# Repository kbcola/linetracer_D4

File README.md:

# linetracer_D4_8
KCCT-D4 ライントレーサー実験 8班

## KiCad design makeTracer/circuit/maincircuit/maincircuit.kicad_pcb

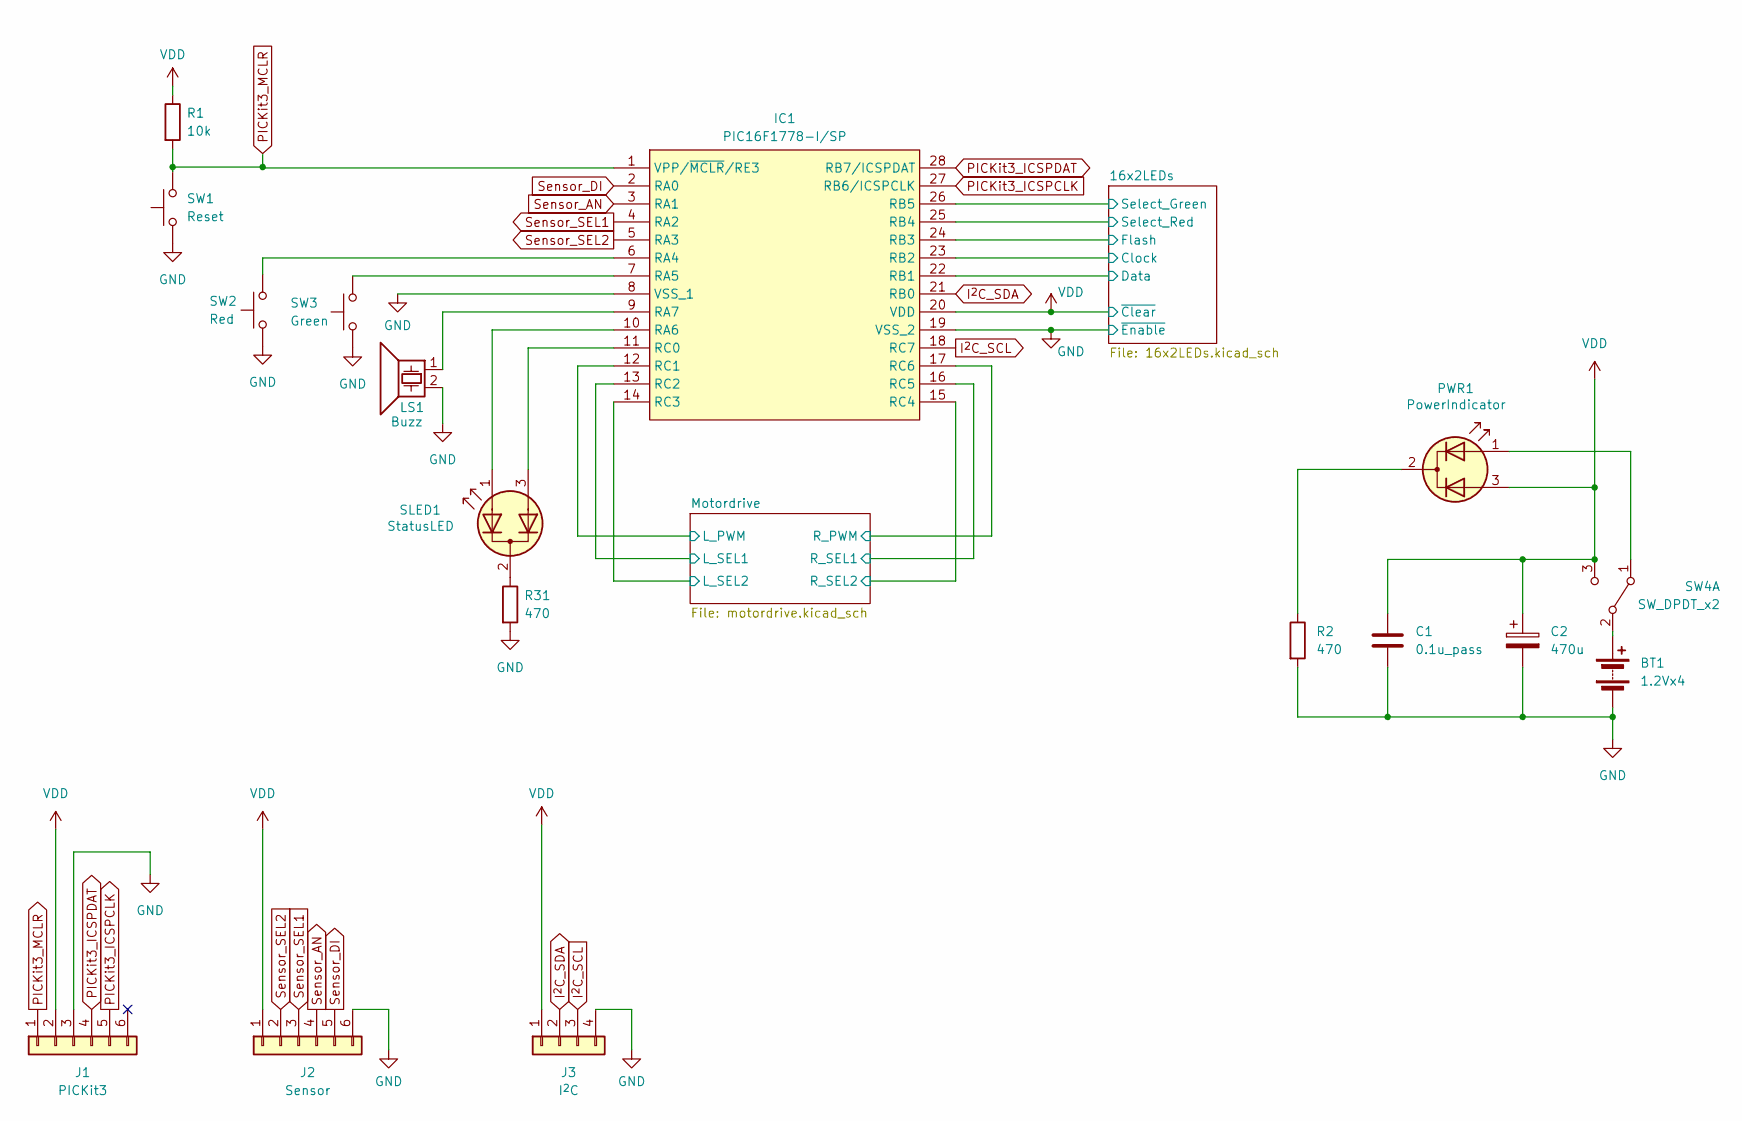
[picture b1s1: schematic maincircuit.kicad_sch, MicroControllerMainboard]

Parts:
BT1: 1.2Vx4; PinHeader_1x02_P2.54mm_Vertical
C1: 0.1u_pass; C_Disc_D5.0mm_W2.5mm_P2.50mm
C2: 470u; CP_Radial_D8.0mm_P3.50mm
IC1: PIC16F1778-I/SP; DIP-28_W7.62mm_Socket_LongPads
J1: PICKit3; PinHeader_1x06_P2.54mm_Vertical
J2: Sensor; SHDR6W69P0X250_1X6_1500X490X1040P
J3: I^{2}C; HDRV4W69P0X250_1X4_1000X500X1040P
LS1: Buzz; Buzzer_TDK_PS1240P02BT_D12.2mm_H6.5mm
PWR1: PowerIndicator; LED_D3.0mm-3
R1: 10k; R_Axial_DIN0207_L6.3mm_D2.5mm_P2.54mm_Vertical
R2: 470; R_Axial_DIN0207_L6.3mm_D2.5mm_P5.08mm_Vertical
R31: 470; R_Axial_DIN0207_L6.3mm_D2.5mm_P7.62mm_Horizontal
SLED1: StatusLED; LED_D3.0mm-3
SW1: Reset; SW_PUSH_6mm_H5mm
SW2: Red; SW_PUSH_6mm_H5mm
SW3: Green; SW_PUSH_6mm_H5mm
SW4: SW_DPDT_x2; ToggleSW_3pin

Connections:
/16x2LEDs/Clock: IC1.23 (RB2); also elsewhere on the board
/16x2LEDs/Data: IC1.22 (RB1); also elsewhere on the board
/16x2LEDs/Flash: IC1.24 (RB3); also elsewhere on the board
/16x2LEDs/Select_Green: IC1.26 (RB5); also elsewhere on the board
/16x2LEDs/Select_Red: IC1.25 (RB4); also elsewhere on the board
/Motordrive/L_PWM: IC1.12 (RC1); also elsewhere on the board
/Motordrive/L_SEL1: IC1.13 (RC2); also elsewhere on the board
/Motordrive/L_SEL2: IC1.14 (RC3); also elsewhere on the board
/Motordrive/R_PWM: IC1.17 (RC6); also elsewhere on the board
/Motordrive/R_SEL1: IC1.16 (RC5); also elsewhere on the board
/Motordrive/R_SEL2: IC1.15 (RC4); also elsewhere on the board
GND: BT1.2 (-), C1.2, C2.2, IC1.8 (VSS_1), IC1.19 (VSS_2), J1.3, J2.6, J3.4, LS1.2, R2.2, R31.2, SW1.1, SW2.1, SW3.1; also elsewhere on the board
I^{2}C_SCL: IC1.18 (RC7), J3.3
I^{2}C_SDA: IC1.21 (RB0), J3.2
unnamed: BT1.1 (+), SW4.2 (B)
unnamed: IC1.6 (RA4), SW2.2
unnamed: IC1.7 (RA5), SW3.2
unnamed: IC1.10 (RA6), SLED1.1 (A1)
unnamed: IC1.9 (RA7), LS1.1
unnamed: IC1.11 (RC0), SLED1.3 (A2)
unnamed: PWR1.1 (A1), SW4.1 (A)
unnamed: PWR1.2 (K), R2.1
unnamed: R31.1, SLED1.2 (K)
PICKit3_ICSPCLK: IC1.27 (RB6/ICSPCLK), J1.5
PICKit3_ICSPDAT: IC1.28 (RB7/ICSPDAT), J1.4
PICKit3_MCLR: IC1.1 (VPP/~MCLR/RE3), J1.1, R1.2, SW1.2
Sensor_AN: IC1.3 (RA1), J2.4
Sensor_DI: IC1.2 (RA0), J2.5
Sensor_SEL1: IC1.4 (RA2), J2.3
Sensor_SEL2: IC1.5 (RA3), J2.2
VDD: C1.1, C2.1, IC1.20 (VDD), J1.2, J2.1, J3.1, PWR1.3 (A2), R1.1, SW4.3 (C); also elsewhere on the board

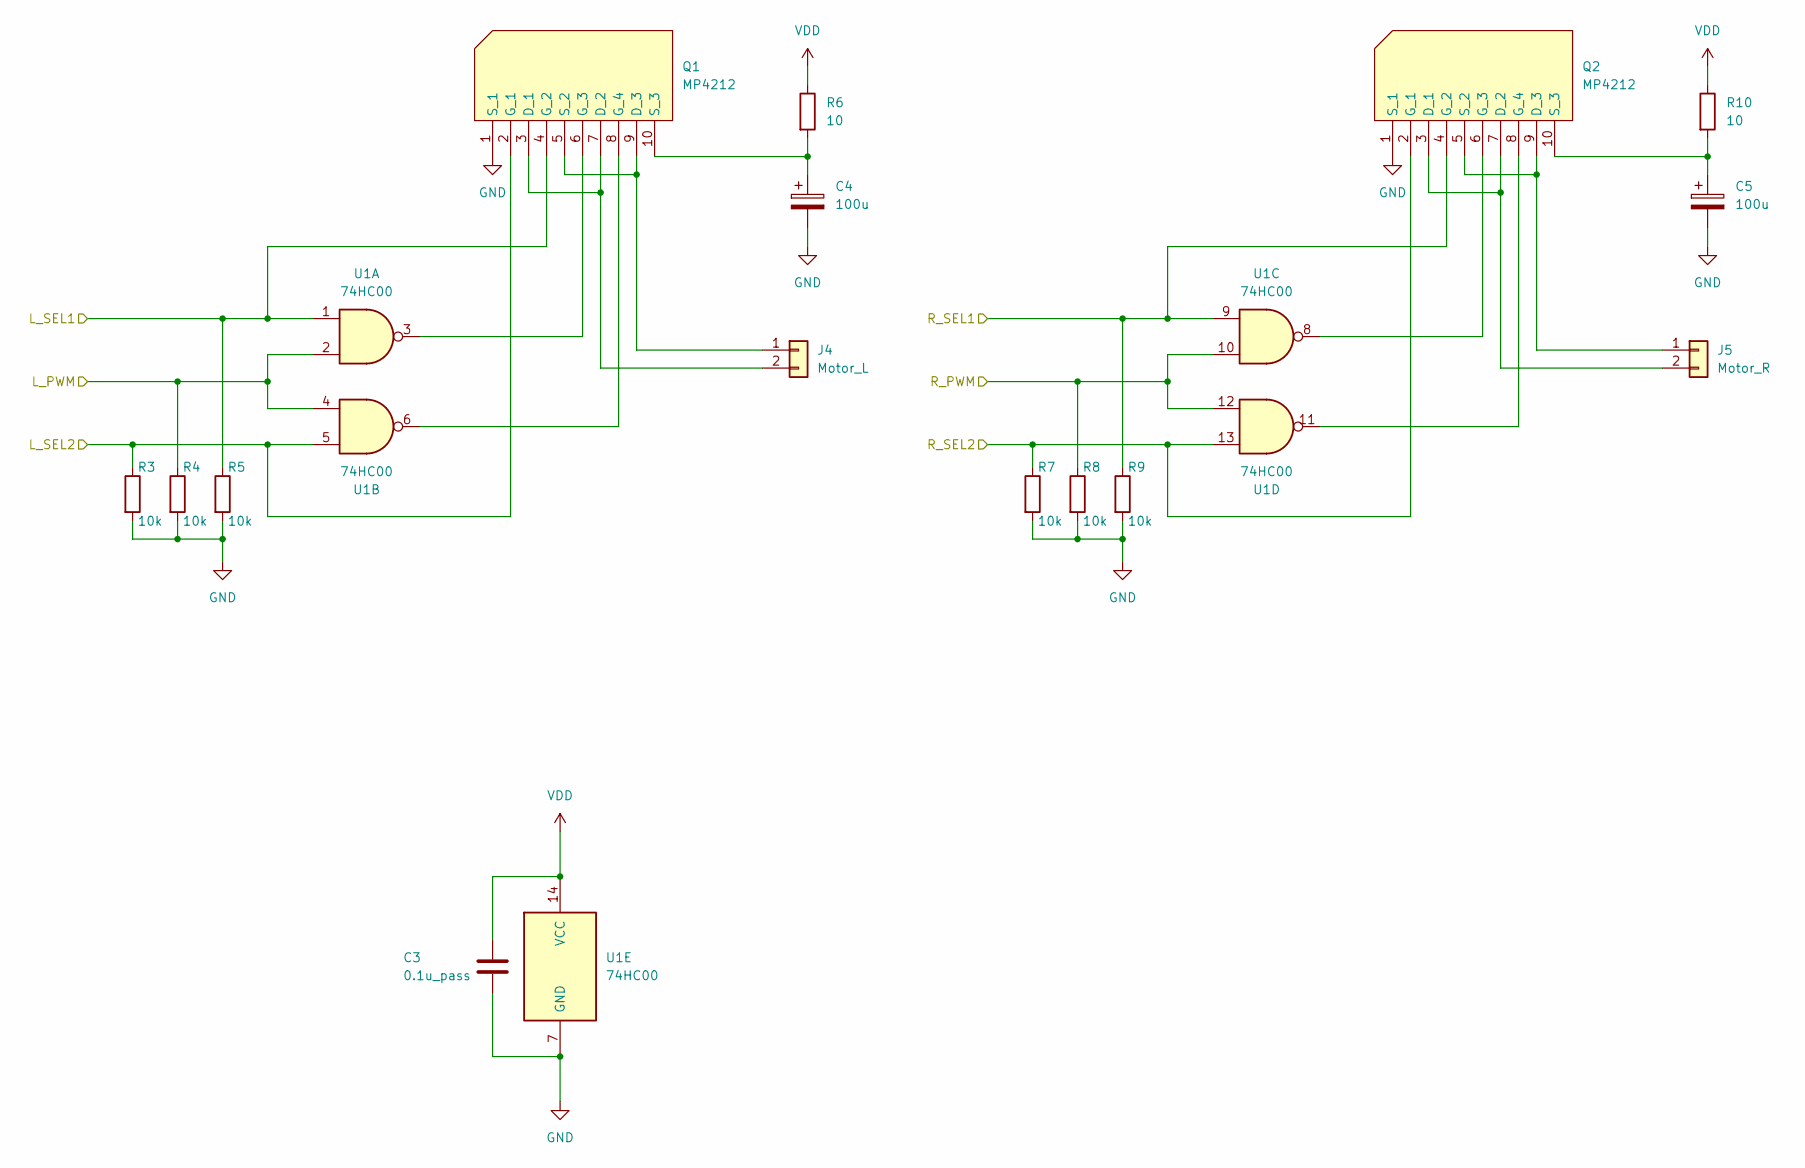
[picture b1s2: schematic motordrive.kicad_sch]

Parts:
C3: 0.1u_pass; C_Disc_D5.0mm_W2.5mm_P2.50mm
C4, C5: 100u; CP_Radial_D5.0mm_P2.00mm
J4: Motor_L; SHDR2W69P0X250_1X2_500X530X1040P
J5: Motor_R; SHDR2W69P0X250_1X2_500X530X1040P
Q1, Q2: MP4212; MP4212_WIDE
R3, R4, R7: 10k; R_Axial_DIN0207_L6.3mm_D2.5mm_P7.62mm_Horizontal
R5: 10k; R_Axial_DIN0207_L6.3mm_D2.5mm_P5.08mm_Vertical
R6: 10; R_Axial_DIN0309_L9.0mm_D3.2mm_P20.32mm_Horizontal
R8, R9: 10k; R_Axial_DIN0207_L6.3mm_D2.5mm_P2.54mm_Vertical
R10: 10; R_Axial_DIN0309_L9.0mm_D3.2mm_P12.70mm_Horizontal
U1: 74HC00; DIP-14_W7.62mm_Socket_LongPads

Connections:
/Motordrive/L_PWM: R4.1, U1.2, U1.4; also elsewhere on the board
/Motordrive/L_SEL1: Q1.4 (G_2), R5.1, U1.1; also elsewhere on the board
/Motordrive/L_SEL2: Q1.2 (G_1), R3.1, U1.5; also elsewhere on the board
/Motordrive/R_PWM: R8.1, U1.10, U1.12; also elsewhere on the board
/Motordrive/R_SEL1: Q2.4 (G_2), R9.1, U1.9; also elsewhere on the board
/Motordrive/R_SEL2: Q2.2 (G_1), R7.1, U1.13; also elsewhere on the board
GND: C3.2, C4.2, C5.2, Q1.1 (S_1), Q2.1 (S_1), R3.2, R4.2, R5.2, R7.2, R8.2, R9.2, U1.7 (GND); also elsewhere on the board
unnamed: J4.1, Q1.5 (S_2), Q1.9 (D_3)
unnamed: J4.2, Q1.3 (D_1), Q1.7 (D_2)
unnamed: J5.1, Q2.5 (S_2), Q2.9 (D_3)
unnamed: J5.2, Q2.3 (D_1), Q2.7 (D_2)
unnamed: Q1.6 (G_3), U1.3
unnamed: Q1.8 (G_4), U1.6
unnamed: C4.1, Q1.10 (S_3), R6.2
unnamed: Q2.6 (G_3), U1.8
unnamed: Q2.8 (G_4), U1.11
unnamed: C5.1, Q2.10 (S_3), R10.2
VDD: C3.1, R6.1, R10.1, U1.14 (VCC); also elsewhere on the board

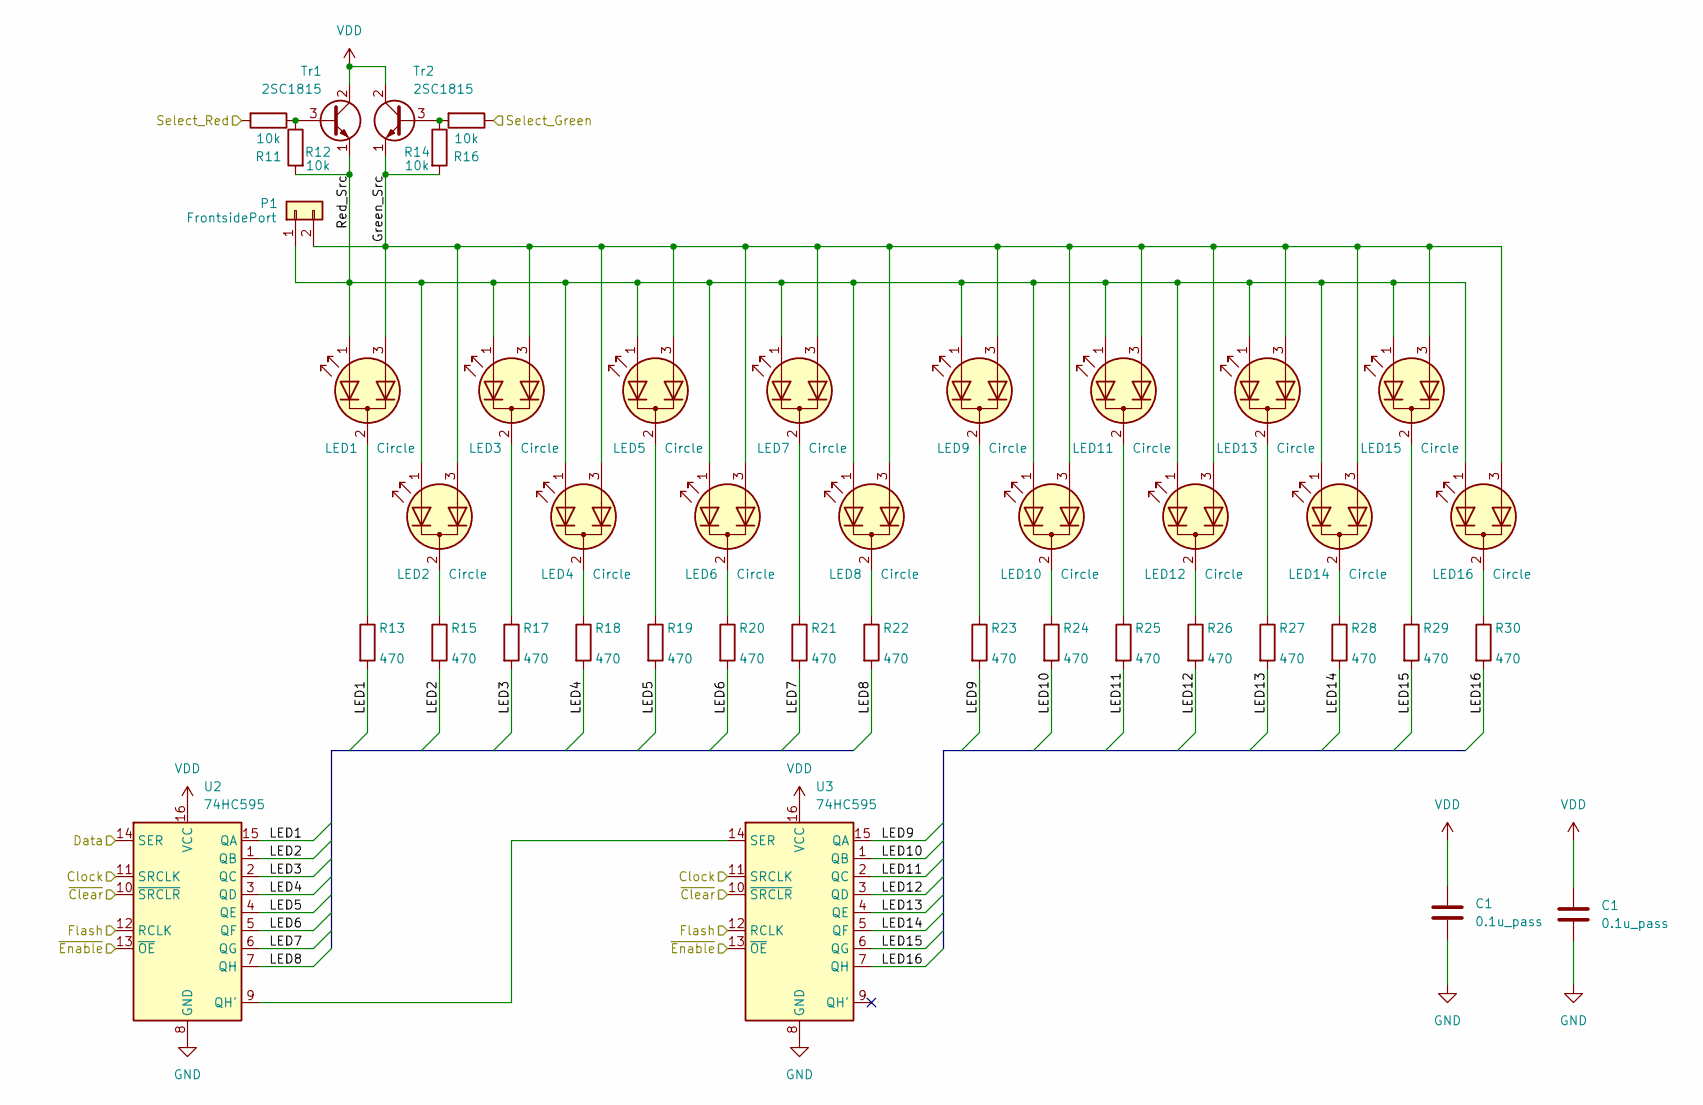
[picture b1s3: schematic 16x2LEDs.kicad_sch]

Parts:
C1: 0.1u_pass; C_Disc_D5.0mm_W2.5mm_P2.50mm
LED1, LED2, LED3, LED4, LED5, LED6, LED7, LED8, LED9, LED10, LED11, LED12, LED13, LED14, LED15, LED16: Circle; LED_D3.0mm-3
P1: FrontsidePort; PinHeader_1x02_P2.54mm_Vertical
R11, R14: 10k; R_Axial_DIN0207_L6.3mm_D2.5mm_P2.54mm_Vertical
R12, R16: 10k; R_Axial_DIN0207_L6.3mm_D2.5mm_P5.08mm_Vertical
R13, R18, R23: 470; R_Axial_DIN0207_L6.3mm_D2.5mm_P10.16mm_Horizontal
R15, R17, R19, R20, R21, R22, R24, R25, R26, R27, R28, R29, R30: 470; R_Axial_DIN0207_L6.3mm_D2.5mm_P7.62mm_Horizontal
Tr1, Tr2: 2SC1815; TO-92_Inline_Wide
U2, U3: 74HC595; DIP-16_W7.62mm_LongPads

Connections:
/16x2LEDs/Clock: U2.11 (SRCLK), U3.11 (SRCLK); also elsewhere on the board
/16x2LEDs/Data: U2.14 (SER); also elsewhere on the board
/16x2LEDs/Flash: U2.12 (RCLK), U3.12 (RCLK); also elsewhere on the board
/16x2LEDs/Green_Src: LED1.3 (A2), LED2.3 (A2), LED3.3 (A2), LED4.3 (A2), LED5.3 (A2), LED6.3 (A2), LED7.3 (A2), LED8.3 (A2), LED9.3 (A2), LED10.3 (A2), LED11.3 (A2), LED12.3 (A2), LED13.3 (A2), LED14.3 (A2), LED15.3 (A2), LED16.3 (A2), P1.2, R14.2, Tr2.1 (E)
/16x2LEDs/LED1: R13.2, U2.15 (QA)
/16x2LEDs/LED2: R15.2, U2.1 (QB)
/16x2LEDs/LED3: R17.2, U2.2 (QC)
/16x2LEDs/LED4: R18.2, U2.3 (QD)
/16x2LEDs/LED5: R19.2, U2.4 (QE)
/16x2LEDs/LED6: R20.2, U2.5 (QF)
/16x2LEDs/LED7: R21.2, U2.6 (QG)
/16x2LEDs/LED8: R22.2, U2.7 (QH)
/16x2LEDs/LED9: R23.2, U3.15 (QA)
/16x2LEDs/LED10: R24.2, U3.1 (QB)
/16x2LEDs/LED11: R25.2, U3.2 (QC)
/16x2LEDs/LED12: R26.2, U3.3 (QD)
/16x2LEDs/LED13: R27.2, U3.4 (QE)
/16x2LEDs/LED14: R28.2, U3.5 (QF)
/16x2LEDs/LED15: R29.2, U3.6 (QG)
/16x2LEDs/LED16: R30.2, U3.7 (QH)
/16x2LEDs/Red_Src: LED1.1 (A1), LED2.1 (A1), LED3.1 (A1), LED4.1 (A1), LED5.1 (A1), LED6.1 (A1), LED7.1 (A1), LED8.1 (A1), LED9.1 (A1), LED10.1 (A1), LED11.1 (A1), LED12.1 (A1), LED13.1 (A1), LED14.1 (A1), LED15.1 (A1), LED16.1 (A1), P1.1, R12.2, Tr1.1 (E)
/16x2LEDs/Select_Green: R16.1; also elsewhere on the board
/16x2LEDs/Select_Red: R11.2; also elsewhere on the board
GND: C1.2, U2.8 (GND), U2.13 (~OE), U3.8 (GND), U3.13 (~OE); also elsewhere on the board
unnamed: LED1.2 (K), R13.1
unnamed: LED2.2 (K), R15.1
unnamed: LED3.2 (K), R17.1
unnamed: LED4.2 (K), R18.1
unnamed: LED5.2 (K), R19.1
unnamed: LED6.2 (K), R20.1
unnamed: LED7.2 (K), R21.1
unnamed: LED8.2 (K), R22.1
unnamed: LED9.2 (K), R23.1
unnamed: LED10.2 (K), R24.1
unnamed: LED11.2 (K), R25.1
unnamed: LED12.2 (K), R26.1
unnamed: LED13.2 (K), R27.1
unnamed: LED14.2 (K), R28.1
unnamed: LED15.2 (K), R29.1
unnamed: LED16.2 (K), R30.1
unnamed: R11.1, R12.1, Tr1.3 (B)
unnamed: R14.1, R16.2, Tr2.3 (B)
unnamed: U2.9 (QH'), U3.14 (SER)
VDD: C1.1, Tr1.2 (C), Tr2.2 (C), U2.10 (~SRCLR), U2.16 (VCC), U3.10 (~SRCLR), U3.16 (VCC); also elsewhere on the board

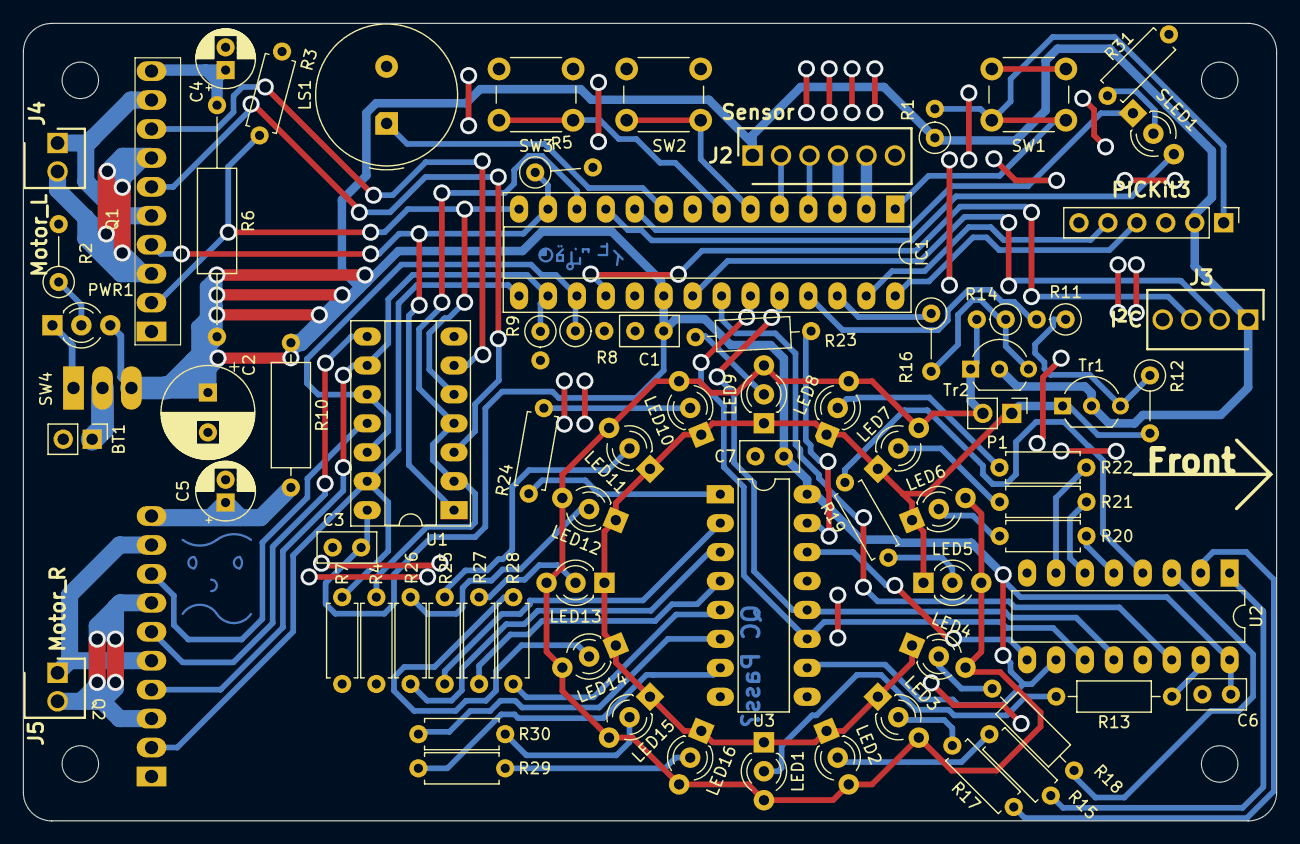
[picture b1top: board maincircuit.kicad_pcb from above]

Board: 2 copper layers, 110.0 x 70.0 mm, 76 parts (1 on the bottom side), 78 nets.

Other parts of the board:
C6, C7: 0.1u_pass; C_Disc_D5.0mm_W2.5mm_P2.50mm

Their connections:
GND: C6.2, C7.2; also elsewhere on the board
VDD: C6.1, C7.1; also elsewhere on the board

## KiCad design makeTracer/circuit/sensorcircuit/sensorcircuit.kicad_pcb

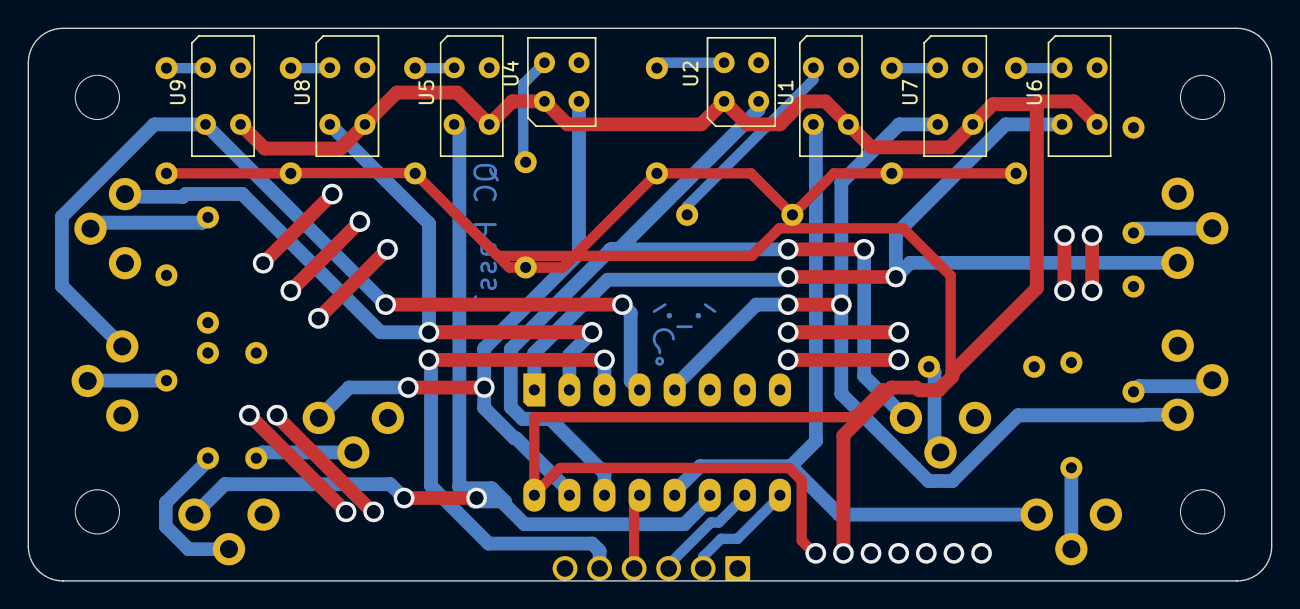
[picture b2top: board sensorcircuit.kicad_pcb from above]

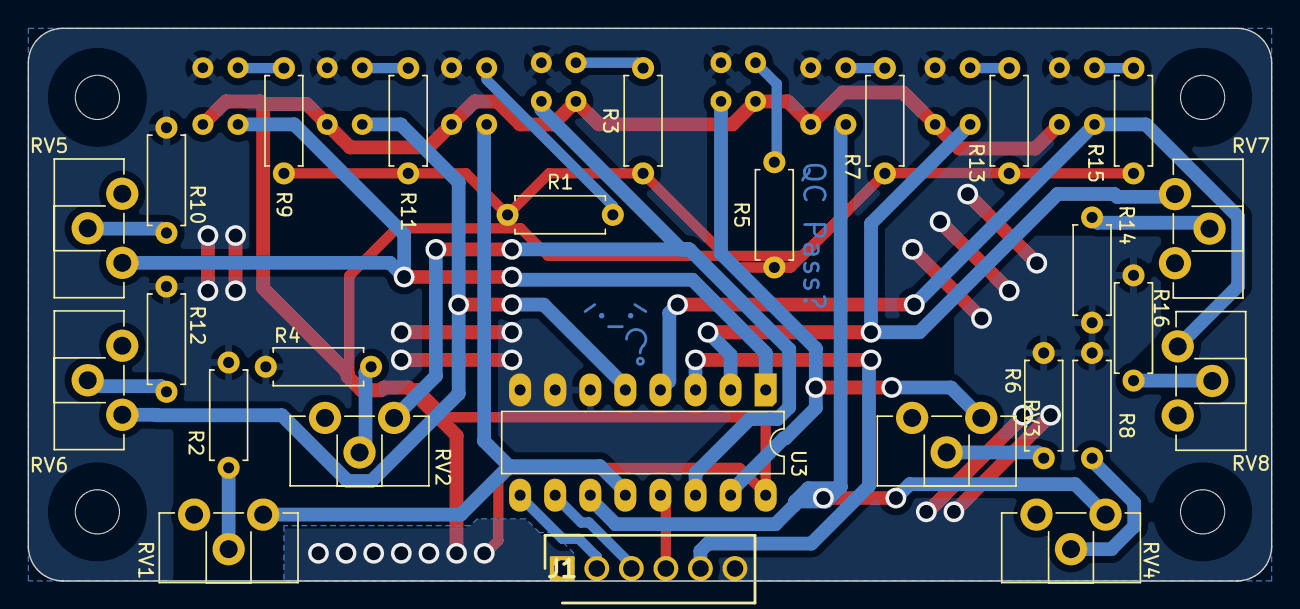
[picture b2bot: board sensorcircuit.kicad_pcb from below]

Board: 2 copper layers, 90.0 x 40.0 mm, 34 parts (26 on the bottom side), 30 nets.

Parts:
J1: Maincircuit; SHDR6W69P0X250_1X6_1500X490X1040P
R1, R3, R5, R7, R9, R11, R13, R15: 220; R_Axial_DIN0207_L6.3mm_D2.5mm_P7.62mm_Horizontal
R2, R4, R6, R8, R10, R12, R14, R16: 100k; R_Axial_DIN0207_L6.3mm_D2.5mm_P7.62mm_Horizontal
RV1, RV2, RV3, RV4, RV5, RV6, RV7, RV8: 50k; Potentiometer_ACP_CA9-H2,5_Horizontal
U1, U5, U6, U7, U8, U9: LBR-127HLD
U2, U4: RPR-220
U3: 4052; DIP-16_W7.62mm_LongPads

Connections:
/Ann_0: RV1.1, U1.3, U3.12 (X0)
/Ann_1: RV2.1, U2.3, U3.14 (X1)
/Ann_2: RV3.1, U3.15 (X2), U4.3
/Ann_3: RV4.1, U3.11 (X3), U5.3
/Dig_0: RV5.1, U3.1 (Y0), U6.3
/Dig_1: RV6.1, U3.5 (Y1), U7.3
/Dig_2: RV7.1, U3.2 (Y2), U8.3
/Dig_3: RV8.1, U3.4 (Y3), U9.3
Analog_Process: J1.4, U3.13 (X)
Digital_Process: J1.5, U3.3 (Y)
GND: J1.6, R2.2, R4.2, R6.2, R8.2, R10.2, R12.2, R14.2, R16.2, U1.2, U2.2, U3.6 (Inh), U3.7 (VEE), U3.8 (VSS), U4.2, U5.2, U6.2, U7.2, U8.2, U9.2
unnamed: R1.2, U1.1
unnamed: R2.1, RV1.2
unnamed: R3.2, U2.1
unnamed: R4.1, RV2.2
unnamed: R5.2, U4.1
unnamed: R6.1, RV3.2
unnamed: R7.2, U5.1
unnamed: R8.1, RV4.2
unnamed: R9.2, U6.1
unnamed: R10.1, RV5.2
unnamed: R11.2, U7.1
unnamed: R12.1, RV6.2
unnamed: R13.2, U8.1
unnamed: R14.1, RV7.2
unnamed: R15.2, U9.1
unnamed: R16.1, RV8.2
Port_SEL1: J1.3, U3.10 (A)
Port_SEL2: J1.2, U3.9 (B)
VDD: J1.1, R1.1, R3.1, R5.1, R7.1, R9.1, R11.1, R13.1, R15.1, U1.4, U2.4, U3.16 (VDD), U4.4, U5.4, U6.4, U7.4, U8.4, U9.4

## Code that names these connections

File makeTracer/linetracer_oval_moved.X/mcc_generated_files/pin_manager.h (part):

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// get/set channel_AN0 aliases
#define channel_AN0_TRIS                 TRISAbits.TRISA0
#define channel_AN0_LAT                  LATAbits.LATA0
#define channel_AN0_PORT                 PORTAbits.RA0
#define channel_AN0_WPU                  WPUAbits.WPUA0
#define channel_AN0_OD                   ODCONAbits.ODA0
#define channel_AN0_ANS                  ANSELAbits.ANSA0
#define channel_AN0_SetHigh()            do { LATAbits.LATA0 = 1; } while(0)
#define channel_AN0_SetLow()             do { LATAbits.LATA0 = 0; } while(0)
#define channel_AN0_Toggle()             do { LATAbits.LATA0 = ~LATAbits.LATA0; } while(0)
#define channel_AN0_GetValue()           PORTAbits.RA0
#define channel_AN0_SetDigitalInput()    do { TRISAbits.TRISA0 = 1; } while(0)
#define channel_AN0_SetDigitalOutput()   do { TRISAbits.TRISA0 = 0; } while(0)
#define channel_AN0_SetPullup()          do { WPUAbits.WPUA0 = 1; } while(0)
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// get/set channel_AN1 aliases
#define channel_AN1_TRIS                 TRISAbits.TRISA1
#define channel_AN1_LAT                  LATAbits.LATA1
#define channel_AN1_PORT                 PORTAbits.RA1
#define channel_AN1_WPU                  WPUAbits.WPUA1
#define channel_AN1_OD                   ODCONAbits.ODA1
#define channel_AN1_ANS                  ANSELAbits.ANSA1
#define channel_AN1_SetHigh()            do { LATAbits.LATA1 = 1; } while(0)
#define channel_AN1_SetLow()             do { LATAbits.LATA1 = 0; } while(0)
#define channel_AN1_Toggle()             do { LATAbits.LATA1 = ~LATAbits.LATA1; } while(0)
#define channel_AN1_GetValue()           PORTAbits.RA1
#define channel_AN1_SetDigitalInput()    do { TRISAbits.TRISA1 = 1; } while(0)
#define channel_AN1_SetDigitalOutput()   do { TRISAbits.TRISA1 = 0; } while(0)
#define channel_AN1_SetPullup()          do { WPUAbits.WPUA1 = 1; } while(0)
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// get/set SENS_SEL1 aliases
#define SENS_SEL1_TRIS                 TRISAbits.TRISA2
#define SENS_SEL1_LAT                  LATAbits.LATA2
#define SENS_SEL1_PORT                 PORTAbits.RA2
#define SENS_SEL1_WPU                  WPUAbits.WPUA2
#define SENS_SEL1_OD                   ODCONAbits.ODA2
#define SENS_SEL1_ANS                  ANSELAbits.ANSA2
#define SENS_SEL1_SetHigh()            do { LATAbits.LATA2 = 1; } while(0)
#define SENS_SEL1_SetLow()             do { LATAbits.LATA2 = 0; } while(0)
#define SENS_SEL1_Toggle()             do { LATAbits.LATA2 = ~LATAbits.LATA2; } while(0)
#define SENS_SEL1_GetValue()           PORTAbits.RA2
#define SENS_SEL1_SetDigitalInput()    do { TRISAbits.TRISA2 = 1; } while(0)
#define SENS_SEL1_SetDigitalOutput()   do { TRISAbits.TRISA2 = 0; } while(0)
#define SENS_SEL1_SetPullup()          do { WPUAbits.WPUA2 = 1; } while(0)
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// get/set SENS_SEL2 aliases
#define SENS_SEL2_TRIS                 TRISAbits.TRISA3
#define SENS_SEL2_LAT                  LATAbits.LATA3
#define SENS_SEL2_PORT                 PORTAbits.RA3
#define SENS_SEL2_WPU                  WPUAbits.WPUA3
#define SENS_SEL2_OD                   ODCONAbits.ODA3
#define SENS_SEL2_ANS                  ANSELAbits.ANSA3
#define SENS_SEL2_SetHigh()            do { LATAbits.LATA3 = 1; } while(0)
#define SENS_SEL2_SetLow()             do { LATAbits.LATA3 = 0; } while(0)
#define SENS_SEL2_Toggle()             do { LATAbits.LATA3 = ~LATAbits.LATA3; } while(0)
#define SENS_SEL2_GetValue()           PORTAbits.RA3
#define SENS_SEL2_SetDigitalInput()    do { TRISAbits.TRISA3 = 1; } while(0)
#define SENS_SEL2_SetDigitalOutput()   do { TRISAbits.TRISA3 = 0; } while(0)
#define SENS_SEL2_SetPullup()          do { WPUAbits.WPUA3 = 1; } while(0)
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// get/set SW1 aliases
#define SW1_TRIS                 TRISAbits.TRISA4
#define SW1_LAT                  LATAbits.LATA4
#define SW1_PORT                 PORTAbits.RA4
#define SW1_WPU                  WPUAbits.WPUA4
#define SW1_OD                   ODCONAbits.ODA4
#define SW1_ANS                  ANSELAbits.ANSA4
#define SW1_SetHigh()            do { LATAbits.LATA4 = 1; } while(0)
#define SW1_SetLow()             do { LATAbits.LATA4 = 0; } while(0)
#define SW1_Toggle()             do { LATAbits.LATA4 = ~LATAbits.LATA4; } while(0)
#define SW1_GetValue()           PORTAbits.RA4
#define SW1_SetDigitalInput()    do { TRISAbits.TRISA4 = 1; } while(0)
#define SW1_SetDigitalOutput()   do { TRISAbits.TRISA4 = 0; } while(0)
#define SW1_SetPullup()          do { WPUAbits.WPUA4 = 1; } while(0)
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// get/set SW2 aliases
#define SW2_TRIS                 TRISAbits.TRISA5
#define SW2_LAT                  LATAbits.LATA5
#define SW2_PORT                 PORTAbits.RA5
#define SW2_WPU                  WPUAbits.WPUA5
#define SW2_OD                   ODCONAbits.ODA5
#define SW2_ANS                  ANSELAbits.ANSA5
#define SW2_SetHigh()            do { LATAbits.LATA5 = 1; } while(0)
#define SW2_SetLow()             do { LATAbits.LATA5 = 0; } while(0)
#define SW2_Toggle()             do { LATAbits.LATA5 = ~LATAbits.LATA5; } while(0)
#define SW2_GetValue()           PORTAbits.RA5
#define SW2_SetDigitalInput()    do { TRISAbits.TRISA5 = 1; } while(0)
#define SW2_SetDigitalOutput()   do { TRISAbits.TRISA5 = 0; } while(0)
#define SW2_SetPullup()          do { WPUAbits.WPUA5 = 1; } while(0)
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// get/set LED_R aliases
#define LED_R_TRIS                 TRISAbits.TRISA6
#define LED_R_LAT                  LATAbits.LATA6
#define LED_R_PORT                 PORTAbits.RA6
#define LED_R_WPU                  WPUAbits.WPUA6
#define LED_R_OD                   ODCONAbits.ODA6
#define LED_R_SetHigh()            do { LATAbits.LATA6 = 1; } while(0)
#define LED_R_SetLow()             do { LATAbits.LATA6 = 0; } while(0)
#define LED_R_Toggle()             do { LATAbits.LATA6 = ~LATAbits.LATA6; } while(0)
#define LED_R_GetValue()           PORTAbits.RA6
#define LED_R_SetDigitalInput()    do { TRISAbits.TRISA6 = 1; } while(0)
#define LED_R_SetDigitalOutput()   do { TRISAbits.TRISA6 = 0; } while(0)
#define LED_R_SetPullup()          do { WPUAbits.WPUA6 = 1; } while(0)
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// get/set BUZZ aliases
#define BUZZ_TRIS                 TRISAbits.TRISA7
#define BUZZ_LAT                  LATAbits.LATA7
#define BUZZ_PORT                 PORTAbits.RA7
#define BUZZ_WPU                  WPUAbits.WPUA7
#define BUZZ_OD                   ODCONAbits.ODA7
#define BUZZ_SetHigh()            do { LATAbits.LATA7 = 1; } while(0)
#define BUZZ_SetLow()             do { LATAbits.LATA7 = 0; } while(0)
#define BUZZ_Toggle()             do { LATAbits.LATA7 = ~LATAbits.LATA7; } while(0)
#define BUZZ_GetValue()           PORTAbits.RA7
#define BUZZ_SetDigitalInput()    do { TRISAbits.TRISA7 = 1; } while(0)
#define BUZZ_SetDigitalOutput()   do { TRISAbits.TRISA7 = 0; } while(0)
#define BUZZ_SetPullup()          do { WPUAbits.WPUA7 = 1; } while(0)
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#define RB0_SetHigh()            do { LATBbits.LATB0 = 1; } while(0)
#define RB0_SetLow()             do { LATBbits.LATB0 = 0; } while(0)
#define RB0_Toggle()             do { LATBbits.LATB0 = ~LATBbits.LATB0; } while(0)
#define RB0_GetValue()              PORTBbits.RB0
#define RB0_SetDigitalInput()    do { TRISBbits.TRISB0 = 1; } while(0)
#define RB0_SetDigitalOutput()   do { TRISBbits.TRISB0 = 0; } while(0)
#define RB0_SetPullup()             do { WPUBbits.WPUB0 = 1; } while(0)
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// get/set LED_SREG_DAT aliases
#define LED_SREG_DAT_TRIS                 TRISBbits.TRISB1
#define LED_SREG_DAT_LAT                  LATBbits.LATB1
#define LED_SREG_DAT_PORT                 PORTBbits.RB1
#define LED_SREG_DAT_WPU                  WPUBbits.WPUB1
#define LED_SREG_DAT_ANS                  ANSELBbits.ANSB1
#define LED_SREG_DAT_SetHigh()            do { LATBbits.LATB1 = 1; } while(0)
#define LED_SREG_DAT_SetLow()             do { LATBbits.LATB1 = 0; } while(0)
#define LED_SREG_DAT_Toggle()             do { LATBbits.LATB1 = ~LATBbits.LATB1; } while(0)
#define LED_SREG_DAT_GetValue()           PORTBbits.RB1
#define LED_SREG_DAT_SetDigitalInput()    do { TRISBbits.TRISB1 = 1; } while(0)
#define LED_SREG_DAT_SetDigitalOutput()   do { TRISBbits.TRISB1 = 0; } while(0)
#define LED_SREG_DAT_SetPullup()          do { WPUBbits.WPUB1 = 1; } while(0)
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// get/set LED_SREG_CLK aliases
#define LED_SREG_CLK_TRIS                 TRISBbits.TRISB2
#define LED_SREG_CLK_LAT                  LATBbits.LATB2
#define LED_SREG_CLK_PORT                 PORTBbits.RB2
#define LED_SREG_CLK_WPU                  WPUBbits.WPUB2
#define LED_SREG_CLK_ANS                  ANSELBbits.ANSB2
#define LED_SREG_CLK_SetHigh()            do { LATBbits.LATB2 = 1; } while(0)
#define LED_SREG_CLK_SetLow()             do { LATBbits.LATB2 = 0; } while(0)
#define LED_SREG_CLK_Toggle()             do { LATBbits.LATB2 = ~LATBbits.LATB2; } while(0)
#define LED_SREG_CLK_GetValue()           PORTBbits.RB2
#define LED_SREG_CLK_SetDigitalInput()    do { TRISBbits.TRISB2 = 1; } while(0)
#define LED_SREG_CLK_SetDigitalOutput()   do { TRISBbits.TRISB2 = 0; } while(0)
#define LED_SREG_CLK_SetPullup()          do { WPUBbits.WPUB2 = 1; } while(0)
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// get/set LED_SREG_SEND aliases
#define LED_SREG_SEND_TRIS                 TRISBbits.TRISB3
#define LED_SREG_SEND_LAT                  LATBbits.LATB3
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
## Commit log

2023-06-18 jikken2: make circuit
2023-06-18 jikken2: fix circuit
2023-06-26 add: pic micon
2023-07-11 comparator ugokan
2023-08-18 wipp
2023-08-19 wippu
2023-08-19 rmdir: iran
2023-08-21 done: maincircuit
2023-08-22 fix: yabai jumper
2023-08-22 great wip
2023-08-23 fix: libraries, absPass -> relPass
2023-08-23 add: sensors and etc.
2023-08-25 ohsaycanyouwip
2023-08-25 wrong size! fooo
2023-08-25 wipwipiwiiwp
2023-09-11 complete: circuit
2023-09-12 fix: .2mm to .4mm
2023-09-19 wip kamo shiren na(´･_･`)
2023-09-21 add: SW Handler (UNVERIFIED)
2023-09-22 fix: SW interrupt
2023-09-22 add: sensor
2023-09-22 fuck fuck fuck: motordriver
2023-09-24 ugoitaaaaaaaaaaaaaaaaaayossshaaaaaaaaaaoraaaaaaaaaaaiyatttttttaaaaaaaaaaaaaaa
2023-09-24 add: P control
2023-09-25 complete: p-control and curveBonus
2023-09-25 ugokaneeeeeeeeeeeeeeeeeonwaaaaaaaaaaaaaaaaaaaaaa
2023-09-25 banzaaaaaaaaaaaaaaaaaaaai!!!!!!!!!!!!!!!
2023-09-27 edit: Rsensor to Lsensor
2023-09-29 gaingayoha
2023-10-03 naniwoshitenno?(reading yokosen
2023-10-12 kansouuuuuuuuuuuuuuuuuuuuuuuuuuuuuuuuuuuuuuuuuuuuuuuuuuuuuuuuuuyeahhhhhhhhhhhhhhhhhhhhhhhhhhhhhhhhhhhhhhhhhhhhhhhhhhhhhhhhhhhhhhhhhhhhhhhhhhhhhhhhhhhhhhhhhhhhhhhhhhhhhhhhhhhhhhhhhhhhhhhhhhhhhhhhhhhhh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
2023-12-26 report iyada

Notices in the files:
makeTracer/linetracer_oval_moved.X/mcc_generated_files/pin_manager.h:
(c) 2018 Microchip Technology Inc. and its subsidiaries.
